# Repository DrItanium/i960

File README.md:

Contains c/c++ code and notes that catalog my progress through the programmers 
reference manual of the Intel 80960mc microprocessor.

It is a RISC processor designed by intel in the 80s which they failed to market.
I find the design fascinating and as such am going through the manuals I have 
found on the internet

The sim directory is my first generation simulator which sucks and doesn't work
well. Take a look at the sim3 project instead.

The hardware directory contains very old hardware implementations as a
reference. I have much newer designs that are not public because they are
modular to save money.

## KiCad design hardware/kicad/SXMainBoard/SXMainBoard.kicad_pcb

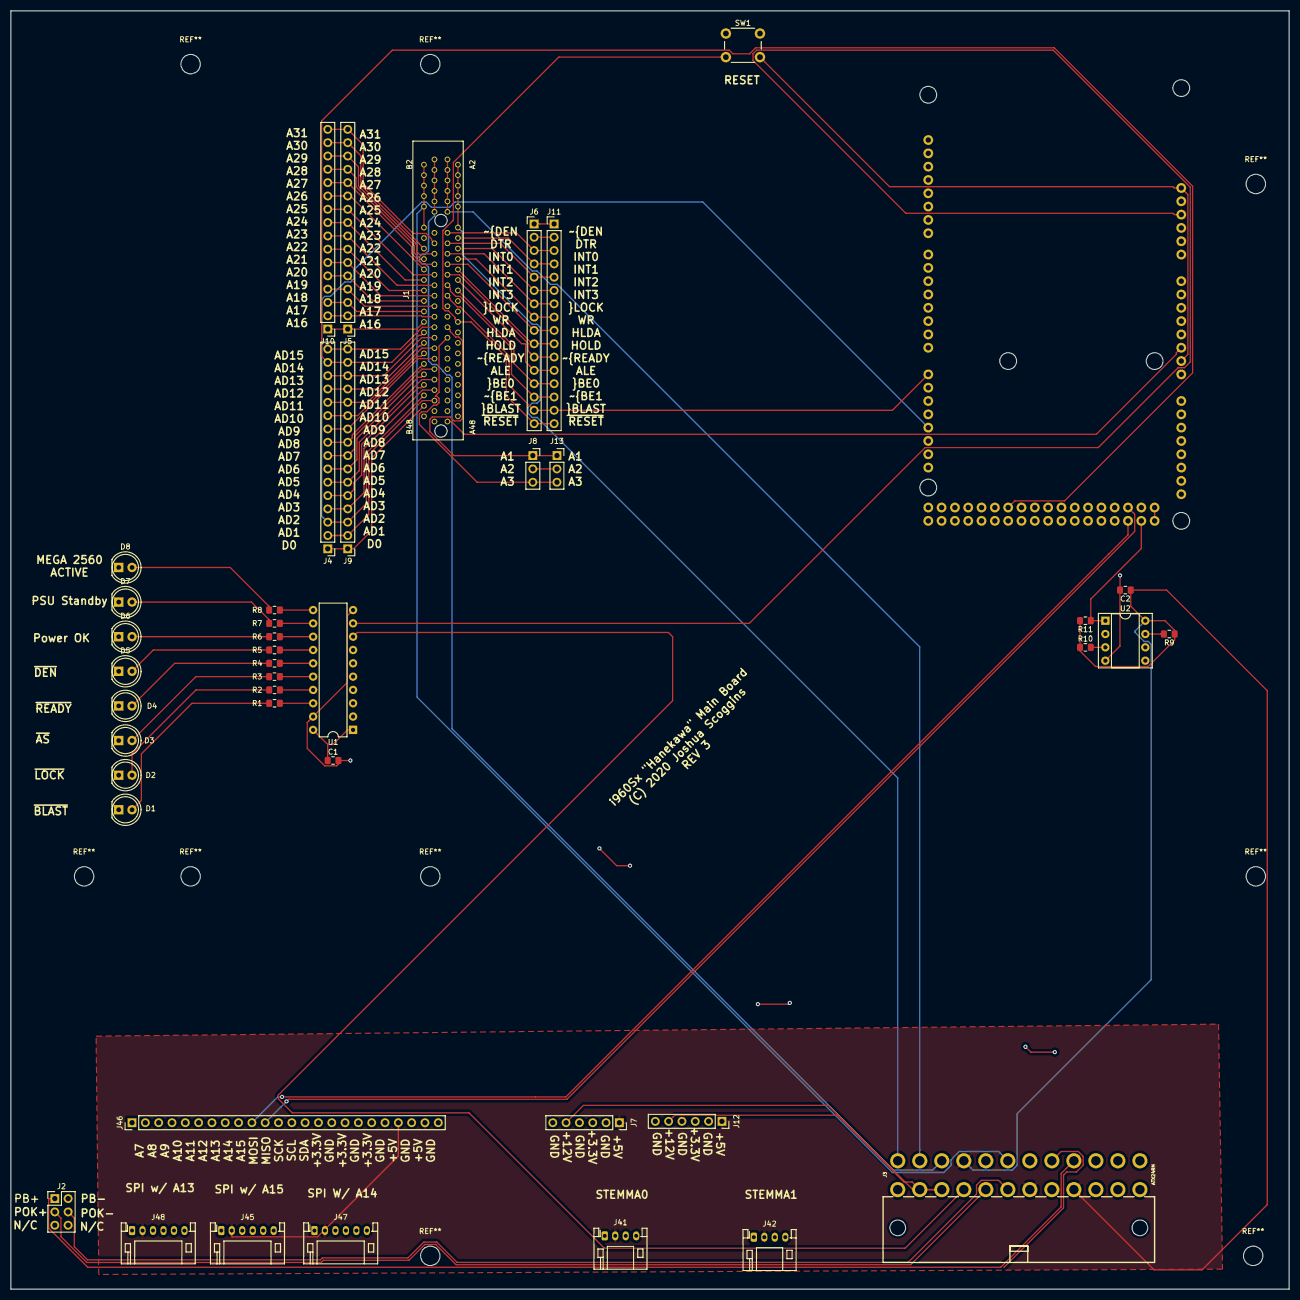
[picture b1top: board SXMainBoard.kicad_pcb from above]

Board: 4 copper layers, 243.8 x 243.8 mm, 44 parts (1 on the bottom side), 100 nets.

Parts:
B1: ARDUINO_MEGA_R3FULL; ARDUINO_MEGA
C1, C2: 0.1uF; C_0805_2012Metric_Pad1.15x1.40mm_HandSolder
D1, D2, D3, D4, D5, D6, D7, D8: LED; LED_D5.0mm
J1: PCIE-098-02-X-D-TH
J2: Conn_02x03_Odd_Even; PinHeader_2x03_P2.54mm_Vertical
J3: ATX24RH; ATX24_RIGHT_ANGLE
J4, J5, J6, J9, J10, J11: Conn_01x16; PinHeader_1x16_P2.54mm_Vertical
J7, J12: Conn_01x06; PinSocket_1x06_P2.54mm_Vertical
J8, J13: Conn_01x03; PinSocket_1x03_P2.54mm_Vertical
J41, J42: CONN_04JST-PTH; JST_PH_S4B-PH-K_1x04_P2.00mm_Horizontal
J45, J47, J48: Conn_01x06; JST_PH_S6B-PH-K_1x06_P2.00mm_Horizontal
J46: Conn_01x24; PinHeader_1x24_P2.54mm_Vertical
R1, R2, R3, R4, R5, R6, R7, R8: 330; R_0805_2012Metric_Pad1.15x1.40mm_HandSolder
R9, R10, R11: 10k; R_0805_2012Metric_Pad1.15x1.40mm_HandSolder
SW1: SW_Push_Dual; SW_PUSH_6mm
U1: 74LS245; DIP-20_W7.62mm
U2: 23LC1024; DIP-8_W7.62mm_Socket

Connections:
+3V3: C1.1, J3.1, J3.2, J3.12, J3.13, J7.3, J12.3, J46.15, J46.17, J46.19, U1.1, U1.20
+5V: C2.1, J3.4, J3.6, J3.21, J7.1, J12.1, J41.2, J42.2, J45.2, J46.21, J46.23, J47.2, J48.2, R9.1, R10.1, R11.2, U2.8
+12V: B1.VIN, J3.10, J3.11, J7.5, J12.5
/A1: B1.A0, J1.A31, J8.1, J13.1
/A2: B1.A1, J1.A32, J8.2, J13.2
/A3: B1.A2, J1.A33, J8.3, J13.3
/A7: B1.A7, J46.1
/A8: B1.A8, J46.2
/A9: B1.A9, J46.3
/A10: B1.A10, J46.4
/A11: B1.A11, J46.5
/A12: B1.A12, J46.6
/A13: B1.A13, J46.7, J48.6
/A14: B1.A14, J46.8, J47.6
/A15: B1.A15, J45.6, J46.9
/A16: B1.34, J1.B30, J5.1, J10.1
/A17: B1.35, J1.B29, J5.2, J10.2
/A18: B1.36, J1.B28, J5.3, J10.3
/A19: B1.37, J1.B27, J5.4, J10.4
/A20: B1.38, J1.B26, J5.5, J10.5
/A21: B1.39, J1.B25, J5.6, J10.6
/A22: B1.40, J1.B24, J5.7, J10.7
/A23: B1.41, J1.B23, J5.8, J10.8
/A24: B1.42, J1.B22, J5.9, J10.9
/A25: B1.43, J1.B21, J5.10, J10.10
/A26: B1.44, J1.B20, J5.11, J10.11
/A27: B1.45, J1.B19, J5.12, J10.12
/A28: B1.46, J1.B18, J5.13, J10.13
/A29: B1.47, J1.B17, J5.14, J10.14
/A30: B1.48, J1.B16, J5.15, J10.15
/A31: B1.49, J1.B15, J5.16, J10.16
/AD1: B1.17, J1.B45, J4.2, J9.2
/AD2: B1.18, J1.B44, J4.3, J9.3
/AD3: B1.19, J1.B43, J4.4, J9.4
/AD4: B1.22, J1.B42, J4.5, J9.5
/AD5: B1.23, J1.B41, J4.6, J9.6
/AD6: B1.24, J1.B40, J4.7, J9.7
/AD7: B1.25, J1.B39, J4.8, J9.8
/AD8: B1.26, J1.B38, J4.9, J9.9
/AD9: B1.27, J1.B37, J4.10, J9.10
/AD10: B1.28, J1.B36, J4.11, J9.11
/AD11: B1.29, J1.B35, J4.12, J9.12
/AD12: B1.30, J1.B34, J4.13, J9.13
/AD13: B1.31, J1.B33, J4.14, J9.14
/AD14: B1.32, J1.B32, J4.15, J9.15
/AD15: B1.33, J1.B31, J4.16, J9.16
/ALE: B1.3, J1.A22, J6.12, J11.12
/CLK2: B1.A5, J1.A49
/D0: B1.16, J1.B46, J4.1, J9.1
/DTR: B1.A4, J1.A48, J6.2, J11.2
/GND0: J1.B2, J1.B4, J1.B6, J1.B8, J1.B10, J1.B12, J3.19
/GND11: J1.A2, J1.A4, J1.A6, J1.A8, J1.A10, J1.A12, J3.24
/HLDA: B1.6, J1.A19, J6.9, J11.9
/HOLD: B1.5, J1.A20, J6.10, J11.10
/INT0: B1.12, J1.A13, J6.3, J11.3
/INT1: B1.11, J1.A14, J6.4, J11.4
/INT2: B1.10, J1.A15, J6.5, J11.5
/INT3: B1.9, J1.A16, J6.6, J11.6
/MEGA_ACTIVE: B1.5V@0, U1.9
/MISO: B1.50, J45.4, J46.11, J47.4, J48.4, U2.2
/MOSI: B1.51, J45.3, J46.10, J47.3, J48.3, U2.5
/POWER_OK: J2.3, J3.8, U1.7
/POWER_OK_GND: J2.4, J3.7
/PSU_STANDBY: J3.9, U1.8
/PWR_ON: J2.1, J3.16
/PWR_ON_GND: J2.2, J3.17
/SCK: B1.52, J45.5, J46.12, J47.5, J48.5, U2.6
/SCL: B1.21, J41.4, J42.4, J46.13
/SDA: B1.20, J41.3, J42.3, J46.14
/VCC0: J1.B1, J1.B3, J1.B5, J1.B7, J1.B9, J1.B11, J3.22
/VCC11: J1.A1, J1.A3, J1.A5, J1.A7, J1.A9, J1.A11, J3.23
/WR: B1.7, J1.A18, J6.8, J11.8
/~AS: B1.15, J1.A29, U1.4
/~BE0: B1.2, J1.A24, J6.13, J11.13
/~BE1: B1.13, J1.A23, J6.14, J11.14
/~BLAST: B1.14, J1.A25, J6.15, J11.15, U1.2
/~DEN: B1.A3, J1.A47, J6.1, J11.1, U1.6
/~LOCK: B1.8, J1.A17, J6.7, J11.7, U1.3
/~READY: B1.4, J1.A21, J6.11, J11.11, U1.5
/~RESET: B1.A6, B1.RESE, J1.A30, J6.16, J11.16, SW1.2
/~SS: B1.53, R11.1, U2.1
GNDREF: C1.2, C2.2, D1.1, D2.1, D3.1, D4.1, D5.1, D6.1, D7.1, D8.1, J3.3, J3.5, J3.15, J3.18, J7.2, J7.4, J7.6, J12.2, J12.4, J12.6, J41.1, J42.1, J45.1, J46.16, J46.18, J46.20, J46.22, J46.24, J47.1, J48.1, SW1.1, U1.10, U1.19, U2.4
unnamed: D1.2, R1.2
unnamed: D2.2, R2.2
unnamed: D3.2, R3.2
unnamed: D4.2, R4.2
unnamed: D5.2, R5.2
unnamed: D6.2, R6.2
unnamed: D7.2, R7.2
unnamed: D8.2, R8.2
unnamed: R1.1, U1.18
unnamed: R2.1, U1.17
unnamed: R3.1, U1.16
unnamed: R4.1, U1.15
unnamed: R5.1, U1.14
unnamed: R6.1, U1.13
unnamed: R7.1, U1.12
unnamed: R8.1, U1.11
unnamed: R9.2, U2.7
unnamed: R10.2, U2.3

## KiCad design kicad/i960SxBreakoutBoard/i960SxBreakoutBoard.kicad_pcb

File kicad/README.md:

# i960 Sx Kicad Projects

As of the time of writing this file there are two projects in here:

- SXMainBoard 
- i960SxBreakoutBoard

The mainboard accepts the custom i960SxBreakoutBoard in a PCI-Express 8x slot
(IT IS NOT ELECTRICALLY PCI-EXPRESS AT ALL)

The main board accepts a mega 2560 so I can analyze the signals coming out of
the i960Sx. I am using a sparkfun ATX connector becuase the i960Sx pulls a
minimum of 3.8A @ 5V! It is a real pig of a CPU at a paltry 10-20Mhz. It runs
_HOT_!

All of the signals are routed into the Mega2560 so I can also use it to emulate
a normal system. I can also mount the board in a standard PC case so that's
really nice.

A special thanks to https://github.com/sparkfun/StupidArduinos (Thanks
Sparkfun, you ROCK!) for publishing the source code to their Pro Micro-ATX. I
lifted the Micro ATX board design directly from it. 

One final thing, if you are curious and get the boards printed please note that they are four layer boards. 
So your choice of pcb manufacturers is quite limited.

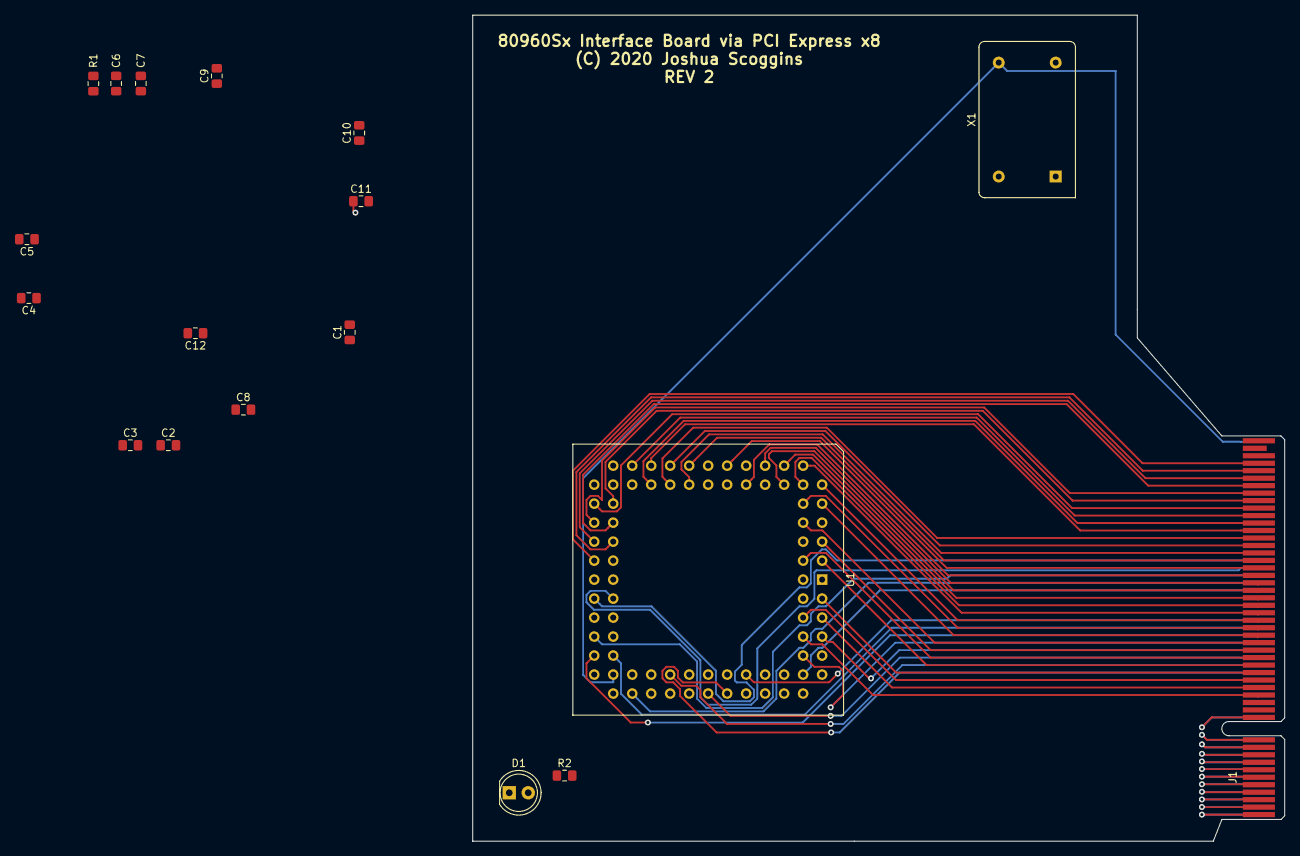
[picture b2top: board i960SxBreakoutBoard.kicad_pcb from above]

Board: 4 copper layers, 108.6 x 110.5 mm, 18 parts (0 on the bottom side), 56 nets.

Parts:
C1, C2, C3, C4, C5, C6, C7, C8, C9, C10, C11, C12: 0.1uF; C_0805_2012Metric_Pad1.15x1.40mm_HandSolder
D1: POWER LED; LED_D5.0mm
J1: PCIE-098-02-X-D-TH; BUS_PCIexpress_x8
R1: 910; R_0805_2012Metric_Pad1.15x1.40mm_HandSolder
R2: 330; R_0805_2012Metric_Pad1.15x1.40mm_HandSolder
U1: 80960Sx; PLCC-84_THT-Socket
X1: OCXO-14; Oscillator_DIP-14

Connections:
+5V: C1.1, C2.1, C3.1, C4.1, C5.1, C6.1, C7.1, C8.1, C9.1, C10.1, C11.1, C12.1, J1.A1, J1.A3, J1.A5, J1.A7, J1.A9, J1.A11, J1.B1, J1.B3, J1.B5, J1.B7, J1.B9, J1.B11, R1.1, R2.2, U1.1, U1.6, U1.17, U1.21, U1.31, U1.33, U1.44, U1.47, U1.53, U1.62, U1.71, U1.73, X1.14
/A1: J1.A31, U1.49
/A2: J1.A32, U1.46
/A3: J1.A33, U1.45
/A16: J1.B30, U1.16
/A17: J1.B29, U1.15
/A18: J1.B28, U1.14
/A19: J1.B27, U1.13
/A20: J1.B26, U1.12
/A21: J1.B25, U1.11
/A22: J1.B24, U1.10
/A23: J1.B23, U1.9
/A24: J1.B22, U1.8
/A25: J1.B21, U1.5
/A26: J1.B20, U1.4
/A27: J1.B19, U1.3
/A28: J1.B18, U1.83
/A29: J1.B17, U1.82
/A30: J1.B16, U1.81
/A31: J1.B15, U1.80
/AD1: J1.B45, U1.40
/AD2: J1.B44, U1.39
/AD3: J1.B43, U1.38
/AD4: J1.B42, U1.37
/AD5: J1.B41, U1.36
/AD6: J1.B40, U1.35
/AD7: J1.B39, U1.30
/AD8: J1.B38, U1.29
/AD9: J1.B37, U1.28
/AD10: J1.B36, U1.27
/AD11: J1.B35, U1.26
/AD12: J1.B34, U1.25
/AD13: J1.B33, U1.24
/AD14: J1.B32, U1.20
/AD15: J1.B31, U1.19
/ALE: J1.A22, U1.78
/AS_: J1.A29, U1.76
/BE0_: J1.A24, U1.52
/BE1_: J1.A23, U1.51
/BLAST_: J1.A25, U1.69
/CLK2: J1.A49, U1.55, X1.8
/D0: J1.B46, U1.41
/DEN_: J1.A47, U1.67
/DTR: J1.A48, U1.68
/HLDA: J1.A19, U1.61
/HOLD: J1.A20, U1.64
/INT0: J1.A13, U1.57
/INT1: J1.A14, U1.58
/INT2: J1.A15, U1.59
/INT3: J1.A16, U1.60
/LOCK_: J1.A17, R1.2, U1.70
/READY_: J1.A21, U1.79
/RESET_: J1.A30, U1.56
/WR: J1.A18, U1.66
GND: C1.2, C2.2, C3.2, C4.2, C5.2, C6.2, C7.2, C8.2, C9.2, C10.2, C11.2, C12.2, J1.A2, J1.A4, J1.A6, J1.A8, J1.A10, J1.A12, J1.B2, J1.B4, J1.B6, J1.B8, J1.B10, J1.B12, U1.7, U1.18, U1.22, U1.32, U1.34, U1.43, U1.48, U1.54, U1.63, U1.72, U1.74, U1.77, U1.84, X1.7
unnamed: D1.2, R2.1

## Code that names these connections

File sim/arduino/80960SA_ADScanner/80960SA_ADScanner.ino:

// A mega2560 sketch to inspect the data lines / address lines of the 80960SA
// processor. This will grow organically but first lets take a look at the
// BE1,BE0, and BLAST_ pins
constexpr auto END0 = 19;
constexpr auto START0 = 2;
constexpr auto READY_ = 18;
constexpr auto ALE = 17;
constexpr auto AS_ = 16;
constexpr auto LOCK_ = 15;
constexpr auto DTR_ = 14;
constexpr auto WR_ = 13;
constexpr auto DEN_ = 12;
constexpr auto HOLD = 11;
constexpr auto INT3_INTA_ = 10;
constexpr auto HLDA = 9;
constexpr auto INT3_ = 8;
constexpr auto INT2_INTR = 7;
constexpr auto RESET = 6;
constexpr auto INT0_ = 5;
constexpr auto BLAST = 4;
constexpr auto BE1 = 3;
constexpr auto BE0 = 2;
void setup() {
    Serial.begin(9600);
    for (int i = START0; i < END0; ++i) {
        pinMode(i, INPUT);
    }
}
void loop() {
    for (int i = START0; i < END0; ++i) {
        Serial.print((digitalRead(i) * 10) + (20 * (i - START0)));
        Serial.print(" ");
    }
    Serial.println();
    delay(1);
}

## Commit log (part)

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2019-06-23 Added visit wrapper functions to Instruction
2019-06-23 Added overloaded template for easy dispatch
2019-06-23 Use classes to describe all the normal types
2019-06-23 Replace enums in description with variant types
2019-06-23 Generate descriptions at constexpr time
2019-06-23 Greatly simplify the dispatch logic for the time being
2019-06-24 Dynamic invocation dispatch
2019-06-24 Start implementing the decode and dispatch logic
2019-06-24 Implement more decode logic
2019-06-24 selectRegister is now a single class method
2019-06-24 Implement memory format instructions
2019-06-24 Implement the final missing instructions for dispatch
2019-06-24 Finished reimplementing dispatch logic
2019-08-28 Define the REGFormatInstruction
    Once a decoded instruction is granted, we construct an appropriate
    instruction kind
2019-08-29 DecodedInstruction now always operates on 12-bit opcodes
    It also holds 64-bits worth of opcodes
2019-08-29 Keep working on the design of Instruction
2019-09-11 Simplify the masking operations
2019-09-11 More implementation bodies
2019-09-11 Added MEMFormatInstruction constructor
2019-09-11 Merge MEMA and MEMB into a single class
    While it is less space efficient, the number of variant entries drops
    from 6 to 5 for instruction!
    This change also abstracts the format of the mem operation from invoking
    part of the simulator.
2019-09-11 Added documentation
2019-09-11 Implement CTRLFormatInstruction
2019-09-12 Fix bugs
2019-09-12 Implement getters for the flags in the proper way
2019-09-12 Start implementing the opcode encode operations
2019-09-12 Bug fixes
2019-09-12 Use decodeSrcDest in more places
2019-09-12 decodeSrc1
2019-09-12 Implemented CTRLFormat instruction encoding
2019-09-12 Implemented COBR instruction building
2019-09-12 DecodedInstruction will now convert to one of the four types
2019-09-12 Starting to support mem fmt
2019-09-18 Remove the old instruction union
2019-09-18 Fixed errors in sim960jx
2019-09-18 Fix up pieces of decode960jx
2019-09-18 Fix more errors
2019-09-19 Use the type field in Operand effectively
2019-09-19 COBR has a flags class now
2019-09-19 Get rid of the bitPosition variable (unused)
2019-09-19 Fix all of the address modes
2019-09-19 moved the opcode classes to opcodes.h
2019-09-19 Use OpcodeValue type
2019-09-19 define opcodeIsInRange
2019-09-20 Flags have a parent type now
2019-09-20 Parent type is not responsible for the variant anymore
2019-09-20 Templatize the dispatch of an instruction fully
2019-09-20 performOperation then dispatchOperation
2019-09-20 Force unimplemented operations for the time being
2019-09-20 Start reimplementing operations
2019-09-20 Fix up things
2019-09-20 More header implementation
2019-09-20 More signature advancements
2019-09-20 Auto generate the method signatures inside of core
2019-09-21 Cut down on typing
2019-09-21 Fix more compiler errors
2019-09-21 Implement more operations to implement
2019-09-24 implement more reg operations
2019-09-24 Fix compile errors
2019-09-24 Clean up code to use performOperation
2019-09-24 Fix compile errors dealing with condition code checks
2019-09-24 reimplement modpc
2019-09-24 Reimplement modtc and modac
2019-09-24 reimplement bbc and bbs
2019-09-24 Rewrite fault operations
2019-09-24 Make sure that we have correct branch dispatch logic
2019-09-24 Rearrange the opcodes data file
2019-09-25 select operations have been migrated
2019-09-25 cleanup dispatcher and opcodes
2019-09-25 Integrate branch code into branchIfGeneric
2019-09-25 Remove bbs decl
2019-09-25 Upgrade alterbit
2019-09-25 transfer calls
2019-09-25 Pull the code from old dispatcher back in.
    It has the effective address calculation code but disabled.
2019-09-26 Fix compilation error
2019-09-26 noexcept specification missing
2019-09-26 dcctl, icctl, syscall, and others
2019-09-26 fixed some warnings and missing symbols
2019-09-26 cmpos, cmpis, cmpib, cmpob
2019-09-26 cmpinc{i,o}, cmpdec{i,o}
2019-09-26 divo and remo
2019-09-26 mulo, muli
2019-09-26 Modi
2019-09-26 ediv
2019-09-26 Compilation fixes
2019-09-26 reimplement xor as seen in the intel manuals
2019-09-26 Notes
2019-09-27 Abstract details of the arithmetic controls away from core class
2019-09-27 remove old arithmetic controls code
2019-09-27 Update the PMCONRegister
2019-09-27 Fix up process control usage
2019-09-27 Finish implmenting missing instructions
2019-09-27 Compact COBR instructions into a small subset of instructions
2019-09-27 More compilation fixes
2019-09-27 Get rid of the fallback case
2019-09-28 Reduce code size further by manually expanding decls
2019-09-28 Fix rest of compilation errors
2019-09-28 Fix warnings from ycm
2019-09-28 Manually implement decls for reg type instructions to make variant tag dispatch work correctly
2019-09-28 Finished manually declaring methods of reg type
    Now all of the variant tags are appropriately implemented
2019-09-28 Enable -Og by default for now
2019-10-01 Specify nindy
2019-10-01 Added the gnu960 source code found on the cmu website, this is a file dump
    this is why you'll see .html files
2019-10-14 Added templated variables for determining instruction class
2019-10-20 started the arduino sketch for scanning the i960SA's AD lines
2019-10-20 start with the boot up sequence
2019-10-21 Tie format detection to the opcode id
2019-10-21 Fault on instructions requiring an implementation
2019-10-21 Define properties about instructions as flags
    Right now, the flags expand to nothing but when I'm ready then the flags
    will be used in a constexpr capacity
2019-10-21 Define more properties
2019-12-23 Start writing an arduino program to emulate the waveforms of the 80960SA/SB
2019-12-23 Define all of the pins and setup the design for now
2019-12-23 Fix naming
2019-12-30 add 80960SB plcc84 part for fritzing
2019-12-30 Added built version of the 80960SB.fzpz
2019-12-30 Update part
2020-01-08 Strip the union out of arithmetic controls
    Just store the relevant contents in separate fields until the full value
    must be acquired.
2020-01-08 Finished updating the arithmetic controls
    I have also rearranged the core information so it can be used without
    full knowledge of a given chip
2020-01-08 Make ProcedureEntry not use a union
2020-01-08 Clean up more of the union code
2020-01-09 Start on TraceControls
2020-01-09 Move setters to NormalRegister.cc
2020-01-09 Finished cleaning up NormalRegister
    Bye bye unions
2020-01-09 Cleaning up core.cc
2020-01-09 Migrate ProcedureEntry over
2020-01-09 Cleaned up TraceControls
2020-01-09 Added std::get impls for Double and Triple Register
2020-01-09 Added std::get impls for NormalRegister
2020-01-09 trace register modification migrated to TraceControls class
2020-01-09 CoreInformation class now describes the salign constants
2020-01-09 code cleanup
2020-01-10 Common base class for DeviceIdentificationCode
2020-01-10 Cleanup core information to depend on the core description itself
2020-01-10 Redefine builtins
2020-01-10 clean up Hx core series definitions
2020-01-10 Added more static_asserts to check core types
2020-01-10 use decode in as many places as possible
2020-01-10 clean up arithmetic controls further
2020-01-10 Simplify DoubleRegister
2020-01-10 Provide a default load/store double impl for MemoryInterface
2020-01-11 More of the new design implemented
    The format is
    [31,16] => i960 Opcode
    [7,4] => Opcode Class
    [3,0] => Argument layout
    This builds a 32-bit token constant that describes options in such a way
    as to make querying about the opcode really easy at runtime
2020-01-13 Use the new dual "layer" design for opcodes
2020-01-13 Cleanup opcodes.h to plug into the rest of the code
2020-01-13 Delete opcodes.cc
    No longer necessary
2020-01-13 Cleanup PMCON Register so that it doesn't use a union internally
2020-01-13 BConRegister is now a class
2020-01-13 added end namespace comment to PMCONRegister
2020-01-16 get rid of const&& as it is wrong
2020-01-16 clean up InternalDataRam.h
2020-01-16 Make records compilable even though it isn't being used
2020-01-16 Simplify some duplicated code with setting condition codes
2020-01-20 Extra actions
2020-01-20 enable_if stuff
2020-01-20 Remove most std::variants from core type dispatch
2020-01-20 subtract and add unconditional are now separate functions
2020-01-20 Conditional add and sub operations are merged in with uncond forms
    The add and subtract is always performed but the corresponding register
    is may or may not be updated based off of the condition codes (if the
    instruction is conditional
2020-01-20 addc is now fully part of the arithmetic template method
2020-01-21 move extended operations to the bottom of the list
2020-01-21 Single CTRL templated method
2020-01-21 cleanup shift operations, found out that overflow fault can be generated for shli
2020-01-21 Moved the 12 bit manipulation operations into a separate method
2020-01-22 clrbit and alterbit are now implemented as bit manipulation fragments
2020-01-22 bbc and bbs merged into cobr performOperation
2020-01-22 Migrate to c++20 and include a tuple template type parameter version of decode
2020-01-22 More use of the shiftmaskpair type
2020-01-22 parameter packs for condition code checking
2020-01-22 Common decode and encode tuples
2020-01-22 More commonization
2020-01-22 Use bit fragment in more places
2020-01-23 More documentation using tuples
2020-01-23 Use BitFragments to make decoding process easier
2020-01-23 paren cleanup
2020-01-23 More BitFragment usage
2020-01-23 use decoder fragment code in more places
2020-01-24 BitFragment is now BitPattern
    Expanded the class so you can describe the set of fields you want to
    extract into a tuple at compile time. Very useful for describing the
    contents of a given bit pattern and then be able to unpack them into a
    tuple in one fell swoop
2020-01-24 decltype elimination
2020-01-24 Initial binary encoder decoder class implementation
2020-01-25 BitFlag
2020-01-25 Use the encoder decoder in REGFlags, fixed a decoding bug too
2020-01-25 Make HasSrcDest responsible for decoding
2020-02-17 Pull in the i960SxBreakoutBoard
2020-02-17 Added a kicad specific readme
2020-02-17 Updated the readme for the kicad stuff to describe where I got the base template from and a little about manufacturing.
2020-02-22 Pull in a bare microatx project for another design
2020-02-28 Start working on v2 of the micro atx
2020-02-29 Perform the correct rename
2020-02-29 More changes
2020-03-01 Start working on the new buffered board design
2020-03-02 Should have 48-bits clocked out of the processor
2020-03-02 Shift out 48 bits as before but d0 isn't captured
2020-03-02 More research into the bus cycles
    Perhaps emulation of these signals is required
2020-05-25 Rename to .cpp so arduino ide can pick it up
2020-05-25 update makefile
2020-05-25 Found a missing rename
2020-05-27 Added the intel960 CTOOLS executables that Rob Krum provided me with
    Very exciting stuff :)
2020-06-06 Starting to fix decoding bugs
2020-06-06 Fixed instruction decoding
2020-06-06 Cleanup the decoding logic for mem type instructions
2020-06-06 Added logic to make emission of decoded instructions valid
2020-06-06 some decode logic cleanup
2020-06-06 Use the BinaryEncoderDecoder structure
2020-06-06 Use the encode decode mechanisms
2020-06-06 Fixed the src/dst ordering
2020-06-06 Clean up encode/decode further
2020-06-06 Don't make instances of bit patterns as it is not necessary
2020-06-06 more core cleanup
2020-06-06 Added numerics bits to arithmetic controls
2020-06-06 Use the BitPattern and encode decode automation in ArithmeticControls
2020-06-06 Make it easy to define deffacts
2020-06-06 More DefFactQuery usage
2020-06-06 ExpandAllOpcodes setup as well
2020-06-06 Save more space by adding class aliases
2020-06-06 More fact queries
2020-06-06 Use BitPattern type
2020-06-07 Use static methods in BitPattern
2020-06-07 Rearrange stuff for testing purposes
2020-06-07 Disable nesting of BinaryEncoderDecoders
    I'm getting compiler errors right now
2020-06-07 I need to track things better so disable the apply routines
2020-07-12 Added a cmakelists for clion support
2020-07-12 Eliminate the old makefile
2020-07-12 update gitignore
2020-07-16 Added Sx based opcodes and disabled the Jx based opcodes
2020-07-16 Re-enable the Jx based opcodes but I won't implement them right now
2020-11-15 Import schematics for many devices
2020-11-15 Import i960CS boot init code

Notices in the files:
hardware/kicad/SXMainBoard/SXMainBoard.kicad_pcb:
(C) 2020 Joshua Scoggins
